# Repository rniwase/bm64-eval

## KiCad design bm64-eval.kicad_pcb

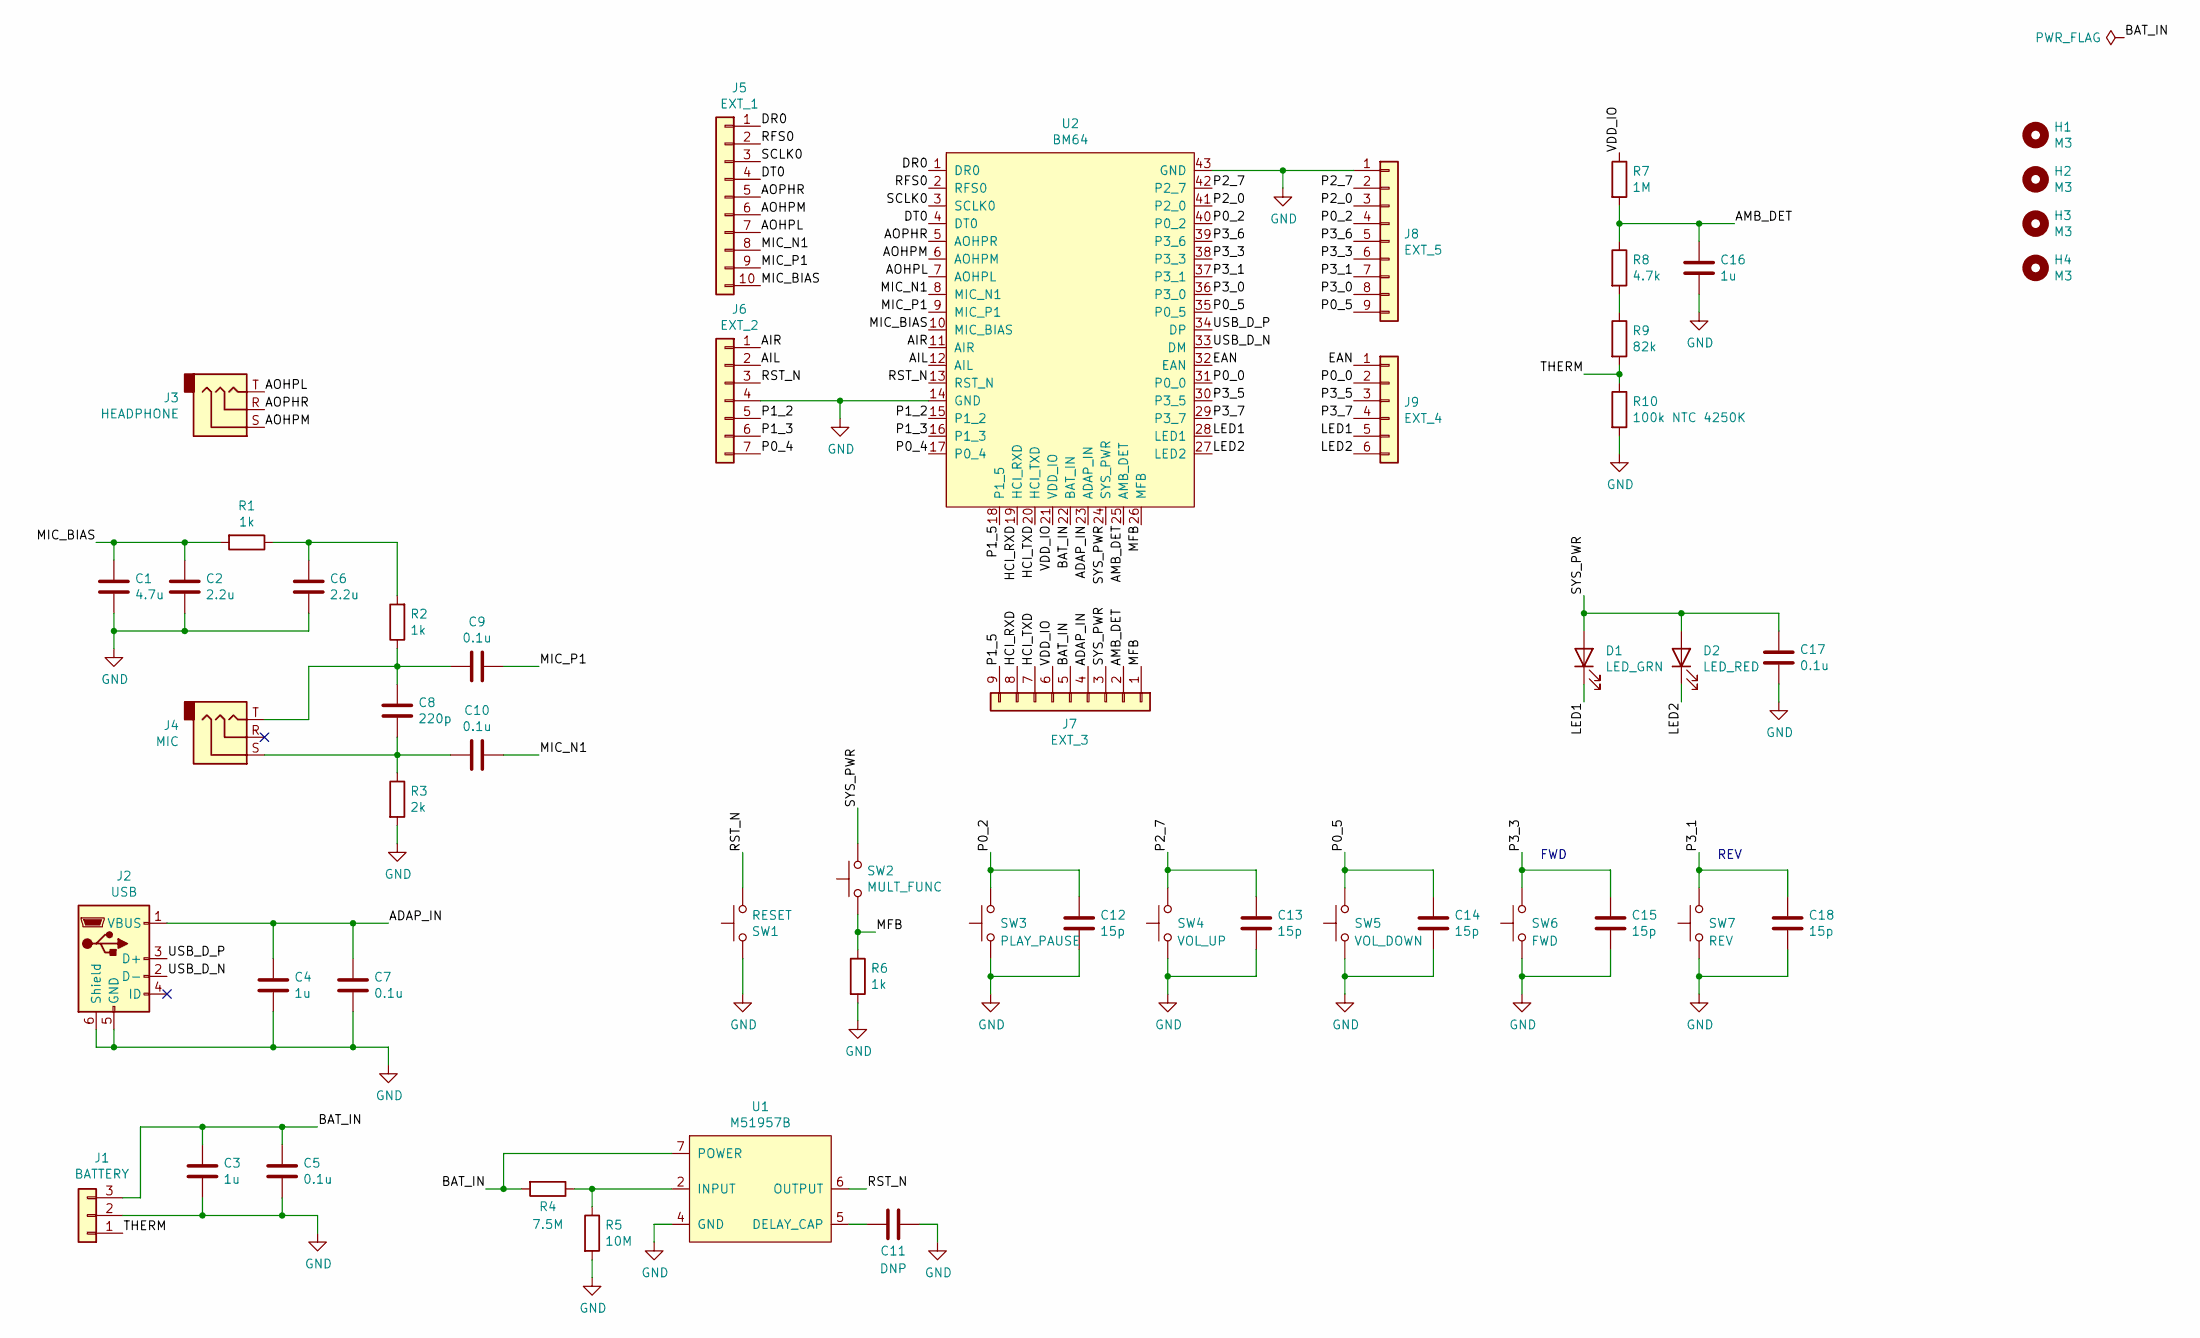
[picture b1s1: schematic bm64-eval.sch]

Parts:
C1: 4.7u; C_0603_1608Metric
C2, C6: 2.2u; C_0603_1608Metric
C3, C4, C16: 1u; C_0603_1608Metric
C5, C7, C9, C10, C17: 0.1u; C_0603_1608Metric
C8: 220p; C_0603_1608Metric
C11: DNP; C_0603_1608Metric
C12, C13, C14, C15, C18: 15p; C_0603_1608Metric
D1: LED_GRN; LED_0603_1608Metric_Castellated
D2: LED_RED; LED_0603_1608Metric_Castellated
H1, H2, H3, H4: M3; MountingHole_3.2mm_M3
J1: BATTERY; JST_PH_B3B-PH-K_1x03_P2.00mm_Vertical
J2: USB; ZX62-B-5PA(33)
J3: HEADPHONE; MJ-8435
J4: MIC; MJ-8435
J5: EXT_1; PinHeader_1x10_P2.54mm_Vertical
J6: EXT_2; PinHeader_1x07_P2.54mm_Vertical
J7: EXT_3; PinHeader_1x09_P2.54mm_Vertical
J8: EXT_5; PinHeader_1x09_P2.54mm_Vertical
J9: EXT_4; PinHeader_1x06_P2.54mm_Vertical
R1, R2, R6: 1k; R_0603_1608Metric
R3: 2k; R_0603_1608Metric
R4: 7.5M; R_0603_1608Metric
R5: 10M; R_0603_1608Metric
R7: 1M; R_0603_1608Metric
R8: 4.7k; R_0603_1608Metric
R9: 82k; R_0603_1608Metric
R10: 100k NTC 4250K; R_0603_1608Metric
SW1: RESET; SW_PUSH_6mm_H5mm
SW2: MULT_FUNC; SW_PUSH_6mm_H5mm
SW3: PLAY_PAUSE; SW_PUSH_6mm_H5mm
SW4: VOL_UP; SW_PUSH_6mm_H5mm
SW5: VOL_DOWN; SW_PUSH_6mm_H5mm
SW6: FWD; SW_PUSH_6mm_H5mm
SW7: REV; SW_PUSH_6mm_H5mm
U1: M51957B; SOP-8_3.76x4.96mm_P1.27mm
U2: BM64

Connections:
/ADAP_IN: C4.1, C7.1, J2.1 (VBUS), J7.4, U2.23 (ADAP_IN)
/AIL: J6.2, U2.12 (AIL)
/AIR: J6.1, U2.11 (AIR)
/AMB_DET: C16.1, J7.2, R7.2, R8.1, U2.25 (AMB_DET)
/AOHPL: J3.T, J5.7, U2.7 (AOHPL)
/AOHPM: J3.S, J5.6, U2.6 (AOHPM)
/AOPHR: J3.R, J5.5, U2.5 (AOHPR)
/BAT_IN: C3.1, C5.1, J1.3, J7.5, R4.2, U1.7 (POWER), U2.22 (BAT_IN)
/DR0: J5.1, U2.1 (DR0)
/DT0: J5.4, U2.4 (DT0)
/EAN: J9.1, U2.32 (EAN)
/HCI_RXD: J7.8, U2.19 (HCI_RXD)
/HCI_TXD: J7.7, U2.20 (HCI_TXD)
/LED1: D1.1 (K), J9.5, U2.28 (LED1)
/LED2: D2.1 (K), J9.6, U2.27 (LED2)
/MFB: J7.1, R6.1, SW2.1, U2.26 (MFB)
/MIC_BIAS: C1.1, C2.1, J5.10, R1.2, U2.10 (MIC_BIAS)
/MIC_N1: C10.1, J5.8, U2.8 (MIC_N1)
/MIC_P1: C9.1, J5.9, U2.9 (MIC_P1)
/P0_0: J9.2, U2.31 (P0_0)
/P0_2: C12.1, J8.4, SW3.2, U2.40 (P0_2)
/P0_4: J6.7, U2.17 (P0_4)
/P0_5: C14.1, J8.9, SW5.2, U2.35 (P0_5)
/P1_2: J6.5, U2.15 (P1_2)
/P1_3: J6.6, U2.16 (P1_3)
/P1_5: J7.9, U2.18 (P1_5)
/P2_0: J8.3, U2.41 (P2_0)
/P2_7: C13.1, J8.2, SW4.2, U2.42 (P2_7)
/P3_0: J8.8, U2.36 (P3_0)
/P3_1: C18.1, J8.7, SW7.2, U2.37 (P3_1)
/P3_3: C15.1, J8.6, SW6.2, U2.38 (P3_3)
/P3_5: J9.3, U2.30 (P3_5)
/P3_6: J8.5, U2.39 (P3_6)
/P3_7: J9.4, U2.29 (P3_7)
/RFS0: J5.2, U2.2 (RFS0)
/RST_N: J6.3, SW1.1, U1.6 (OUTPUT), U2.13 (RST_N)
/SCLK0: J5.3, U2.3 (SCLK0)
/SYS_PWR: C17.1, D1.2 (A), D2.2 (A), J7.3, SW2.2, U2.24 (SYS_PWR)
/THERM: J1.1, R9.2, R10.1
/USB_D_N: J2.2 (D-), U2.33 (DM)
/USB_D_P: J2.3 (D+), U2.34 (DP)
/VDD_IO: J7.6, R7.1, U2.21 (VDD_IO)
GND: C1.2, C2.2, C3.2, C4.2, C5.2, C6.2, C7.2, C11.1, C12.2, C13.2, C14.2, C15.2, C16.2, C17.2, C18.2, J1.2, J2.5 (GND), J2.6 (Shield), J6.4, J8.1, R3.2, R5.2, R6.2, R10.2, SW1.2, SW3.1, SW4.1, SW5.1, SW6.1, SW7.1, U1.4 (GND), U2.14 (GND), U2.43 (GND)
unnamed: C6.1, R1.1, R2.2
unnamed: C8.1, C9.2, J4.T, R2.1
unnamed: C8.2, C10.2, J4.S, R3.1
unnamed: C11.2, U1.5 (DELAY_CAP)
unnamed: R4.1, R5.1, U1.2 (INPUT)
unnamed: R8.2, R9.1

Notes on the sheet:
FWD
REV

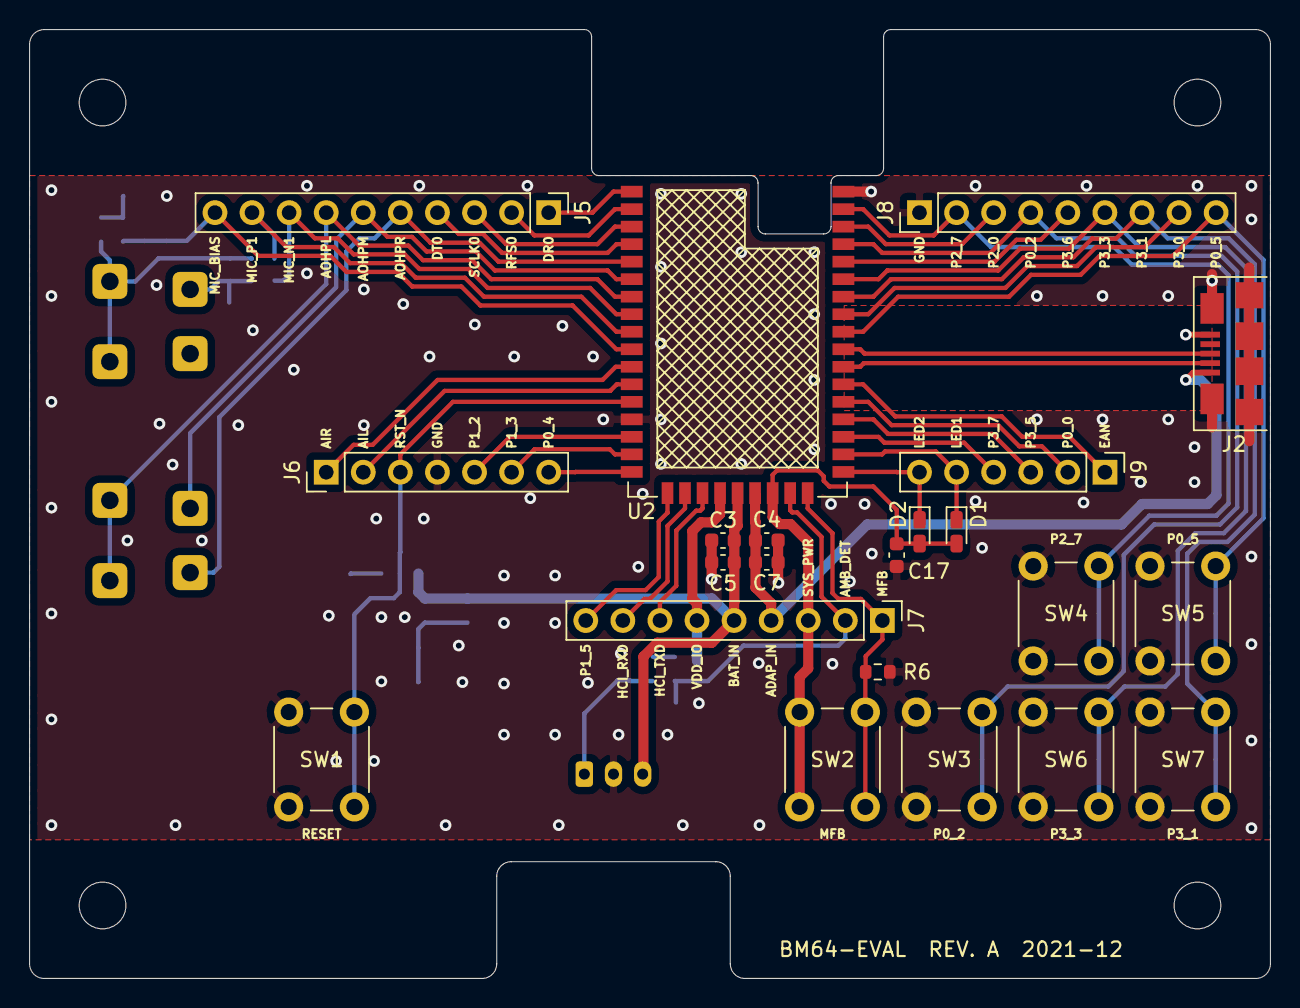
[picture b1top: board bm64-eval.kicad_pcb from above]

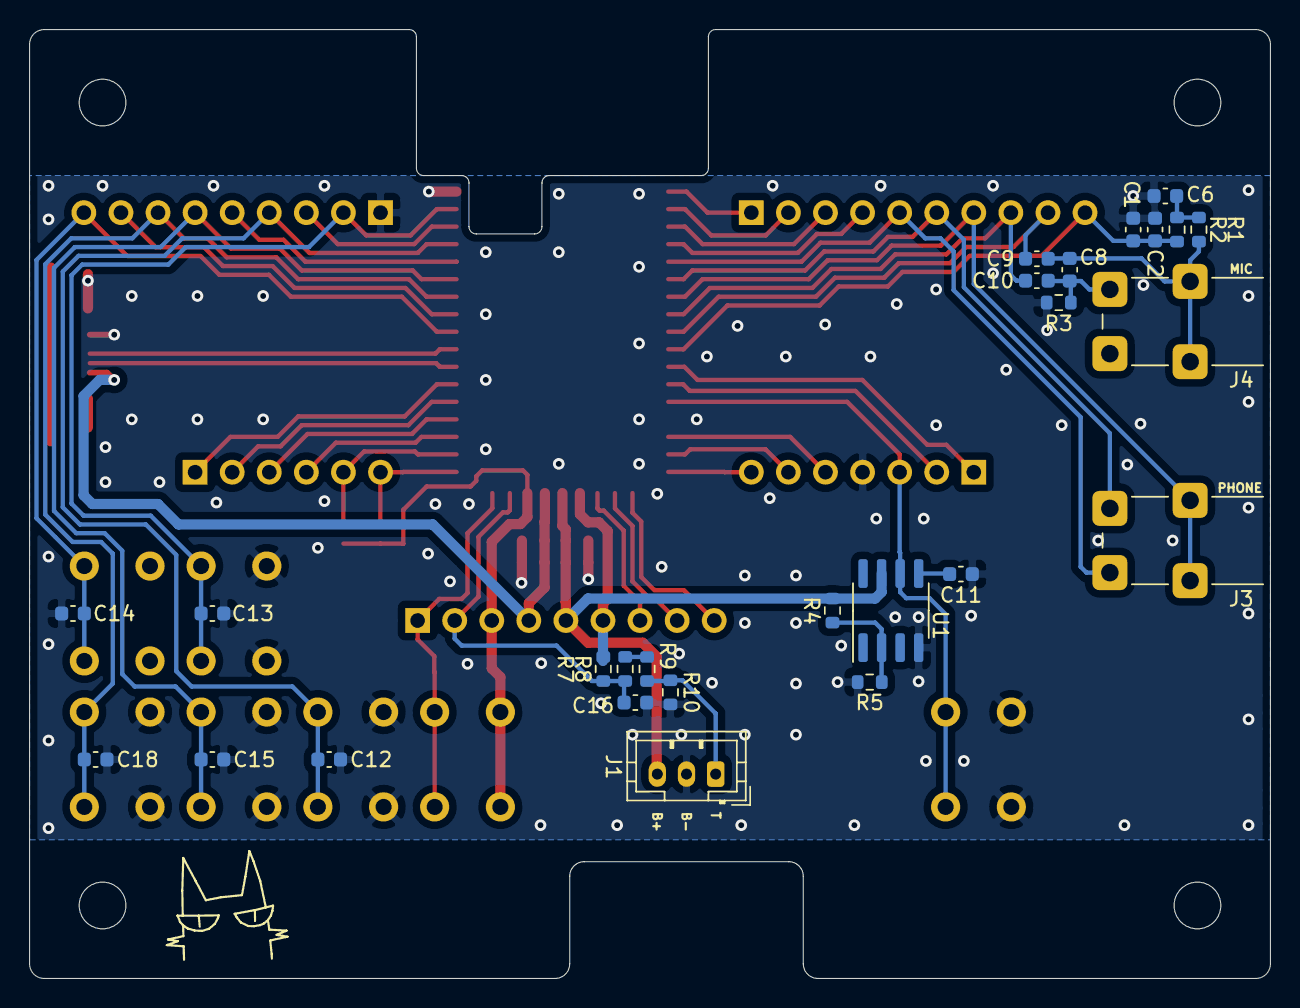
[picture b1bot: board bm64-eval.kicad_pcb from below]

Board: 2 copper layers, 85.0 x 65.0 mm, 52 parts (26 on the bottom side), 49 nets.

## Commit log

2021-11-28 update MJ-8435 footprint
2021-11-30 apply gerber settings
2021-12-18 swap R4 R5 value
